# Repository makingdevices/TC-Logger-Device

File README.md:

<!-- Improved compatibility of back to top link: See: https://github.com/othneildrew/Best-README-Template/pull/73 -->

<!--
*** Thanks for checking out the Best-README-Template. If you have a suggestion
*** that would make this better, please fork the repo and create a pull request
*** or simply open an issue with the tag "enhancement".
*** Don't forget to give the project a star!
*** Thanks again! Now go create something AMAZING! :D
-->

<!-- PROJECT SHIELDS -->
<!--
*** I'm using markdown "reference style" links for readability.
*** Reference links are enclosed in brackets [ ] instead of parentheses ( ).
*** See the bottom of this document for the declaration of the reference variables
*** for contributors-url, forks-url, etc. This is an optional, concise syntax you may use.
*** https://www.markdownguide.org/basic-syntax/#reference-style-links
-->
[![Instagram][ig-shield]][ig-url]
[![PCBWAY][sponsor-shield]][sponsor-url]
[![Stargazers][stars-shield]][stars-url]
[![Issues][issues-shield]][issues-url]
[![LinkedIn][linkedin-shield]][linkedin-url]

<!-- PROJECT LOGO -->
<br />
<div align="center">

<h3 align="center">Making Devices</h3>

  <p align="center">
    Open Source projects where we struggle with engineering, electronics, coding and who knows what else... In this case, TC Logger Device is a very simple USB thermocouple reader, so hopefully you may find it interesting ;)
  </p>
</div>

<!-- TABLE OF CONTENTS -->
<details>
  <summary>Table of Contents</summary>
  <ol>
    <li>
      <a href="#about-the-project">About The Project</a>
      <ul>
        <li><a href="#built-with">Built With</a></li>
      </ul>
    </li>
    <li>
      <a href="#Build-one">Build one</a>
      <ul>
      </ul>
    </li>
    <li><a href="#usage">Usage</a></li>
    <li><a href="#roadmap">Roadmap</a></li>
    <li><a href="#license">License</a></li>
    <li><a href="#contact">Contact</a></li>
    <li><a href="#Sponsor">Sponsor</a></li>
  </ol>
</details>

<!-- ABOUT THE PROJECT -->
## About The Project

[![Bytes Counter Shot][product-screenshot]](https://makingdevices.com/TCLogger-Device)

TC Logger Device is a simple thermocouple USB reader: help you to measure any proccess you need using the USB protocol an a simple software developed in Python. The project was chosen to test the USB communication, explore the interface PC-Embedded system. The project is able to use two thermocouple at the same time and share the data to the computer at a speed of 5Hz. (5 samples per second). The main microprocessor is the PIC18F14K50.

<p align="right">(<a href="#readme-top">back to top</a>)</p>

### Built With

[![Microcontroller][PIC]][PIC-url]
[![MPLAB C][MPLAB-C]][MPLAB-C-url]
[![Kicad][kicad-shield]][kicad-url]
[![SPONSOR][sponsor-icon]][sponsor-url]

<p align="right">(<a href="#readme-top">back to top</a>)</p>

<!-- GETTING STARTED -->

## Build one
The project is finished and no further development will be made. The device is safe, stable and It was tested. 

1. Get the gerber files for the latest version: [V1.2b](https://github.com/makingdevices/TC-Logger-Device/blob/main/Gerber/v1.2b/ThermoDeviceLogger-v_1.2b.zip) 
2. Send them to a PCB manufacturer ([Our Sponsor is PCBWAY][sponsor-url])
3. You can read the user manual: [V1.0](https://github.com/makingdevices/TC-Logger-Device/blob/main/Output_PDF/Manual_ThermoLoggerv1_0.pdf) 

<p align="right">(<a href="#readme-top">back to top</a>)</p>

<!-- USAGE EXAMPLES -->
## Usage

Instructions of use:

- The LED will light up if a thermocouple is not detected.
- Use the Python software to communicate with the board.

You can read the user manual: [V1.0](https://github.com/makingdevices/TC-Logger-Device/blob/main/Output_PDF/Manual_ThermoLoggerv1_0.pdf) 

<p align="right">(<a href="#readme-top">back to top</a>)</p>

<!-- ROADMAP -->
## Roadmap

- [x] Finish the firmware for the PIC18F14K50
- [x] Validate firmware
- [x] Finish PC software
    - [x] Implement SCPI commands 
    - [x] Add data records 
    - [X] Improve thermocouple graphs
    - [x] Add Device Info page

See the [open issues](https://github.com/makingdevices/Thermo-device-logger/issues) for a full list of proposed features (and known issues).

State: Project <b>FINISHED</b> - 26/09/2023

Priority: <b>High</b>

<!-- SCPI -->
## SCPI Commands

- :MEAS  
  - :TC1
    - :INT?
    - :EXT?
    - :LED?
  - :TC2 
    - :INT?
    - :EXT?
    - :LED?
- :SET  
  - :TC1
    - :LED [AUTO|0|1] 
  - :TC2
    - :LED [AUTO|0|1] 
- :MODE   
  - :LED
    - :TC1?
    - :TC2?
- :CONF  
    - :APP?
    - :HW?
- *IDN?  
- :hello? 

<p align="right">(<a href="#readme-top">back to top</a>)</p>

<!-- LICENSE -->
## License

Distributed under three licenses:
- [Hardware](/License/HW_cern_ohl_s_v2.pdf)
- [Software](/License/SW_GPLv3.0.txt)
- [Documentation](/License/Documentation_CC-BY-SA-4.0.txt)

OSHW LICENSE: [ES000034](https://certification.oshwa.org/es000034.html)

[![GPL v3 License][license-shield]][license-url] 
<p align="right">(<a href="#readme-top">back to top</a>)</p>

<!-- CONTACT -->
## Contact

Making Devices - [@MakingDevices](https://www.instagram.com/makingdevices/)

Project Link: [https://github.com/makingdevices/TC-Logger-Device/](https://github.com/makingdevices/TC-Logger-Device/)

Other Links: [LinkTree](https://makingdevices.com/links/)

<p align="right">(<a href="#readme-top">back to top</a>)</p>

<!-- Sponsor -->
## Sponsor

[PCBWAY](https://www.pcbway.com/?from=makingdevices) is the most professional PCB manufacturer for prototyping and low-volume production to work with in the world. With more than a decade in the field, They are committed to meeting the needs of their customers from different industries in terms of quality, delivery, cost-effectiveness and any other demanding requests. As Sponsor of Making Devices, they will be in charge of all the PCBs for MDV, allowing both of us to grow together in a long term partnership. We hope you take them into account for your both personal and professional prototypes or products.

[![Sponsor Shot][sponsor-pcb-1]][sponsor-url]
[![Sponsor Shot][sponsor-pcb-2]][sponsor-url]

Should you want to colaborate with MakingDevices, you can buy a [TC Logger Device fully assembled and ready to use](https://www.pcbway.com/project/gifts_detail/TC_Logger_Device_5464ceb2.html)

<p align="right">(<a href="#readme-top">back to top</a>)</p>

<!-- MARKDOWN LINKS & IMAGES -->
<!-- https://www.markdownguide.org/basic-syntax/#reference-style-links -->
[contributors-shield]: https://img.shields.io/github/contributors/makingdevices/Thermo-device-logger.svg?style=for-the-badge
[contributors-url]: https://github.com/makingdevices/Thermo-device-logger/graphs/contributors
[forks-shield]: https://img.shields.io/github/forks/makingdevices/Thermo-device-logger.svg?style=for-the-badge
[forks-url]: https://github.com/makingdevices/Thermo-device-logger/network/members
[stars-shield]: https://img.shields.io/github/stars/makingdevices/Thermo-device-logger.svg?style=for-the-badge
[stars-url]: https://github.com/makingdevices/Thermo-device-logger/stargazers
[issues-shield]: https://img.shields.io/github/issues/makingdevices/Thermo-device-logger.svg?style=for-the-badge
[issues-url]: https://github.com/makingdevices/Thermo-device-logger/issues
[license-shield]: /images/license.png
[license-url]: https://github.com/makingdevices/Thermo-device-logger/tree/main/License
[linkedin-shield]: https://img.shields.io/badge/-LinkedIn-black.svg?style=for-the-badge&logo=linkedin&colorB=555
[linkedin-url]: https://www.linkedin.com/company/making-devices/
[sponsor-shield]: https://img.shields.io/badge/SPONSOR-PCBWAY-black.svg?style=for-the-badge&colorB=1200
[sponsor-url]: https://www.pcbway.com/?from=makingdevices
[sponsor-screenshot]: /images/PCB_sponsor.png
[sponsor-pcb-1]: /images/TClogger_pcb1.jpg
[sponsor-pcb-2]: /images/TClogger_pcb2.jpg
[product-screenshot]: images/screenshot.jpg
[PIC]: https://img.shields.io/badge/PIC18LF14K50-000000?style=for-the-badge
[PIC-url]: http://ww1.microchip.com/downloads/en/devicedoc/40001350f.pdf
[kicad-shield]: https://img.shields.io/badge/kicad-0b03fc?style=for-the-badge&logo=kicad&logoColor=white
[kicad-url]: https://www.kicad.org/
[YT-screenshot]: images/YT_assembly.PNG
[sponsor-icon]:  https://img.shields.io/badge/-PCBWAY-black.svg?style=for-the-badge&colorB=1200
[ig-shield]: https://img.shields.io/badge/instagram-a83297?style=for-the-badge&logo=instagram&logoColor=white
[ig-url]: https://www.instagram.com/makingdevices/
[MPLAB-C]: https://img.shields.io/badge/MPLAB%20C18-DD0031?style=for-the-badge&logo=C&logoColor=white
[MPLAB-C-url]: https://www.microchip.com/en-us/development-tool/SW006011
[Svelte.dev]: https://img.shields.io/badge/Svelte-4A4A55?style=for-the-badge&logo=svelte&logoColor=FF3E00
[Svelte-url]: https://svelte.dev/
[Laravel.com]: https://img.shields.io/badge/Laravel-FF2D20?style=for-the-badge&logo=laravel&logoColor=white
[Laravel-url]: https://laravel.com
[Bootstrap.com]: https://img.shields.io/badge/Bootstrap-563D7C?style=for-the-badge&logo=bootstrap&logoColor=white
[Bootstrap-url]: https://getbootstrap.com
[JQuery.com]: https://img.shields.io/badge/jQuery-0769AD?style=for-the-badge&logo=jquery&logoColor=white
[JQuery-url]: https://jquery.com

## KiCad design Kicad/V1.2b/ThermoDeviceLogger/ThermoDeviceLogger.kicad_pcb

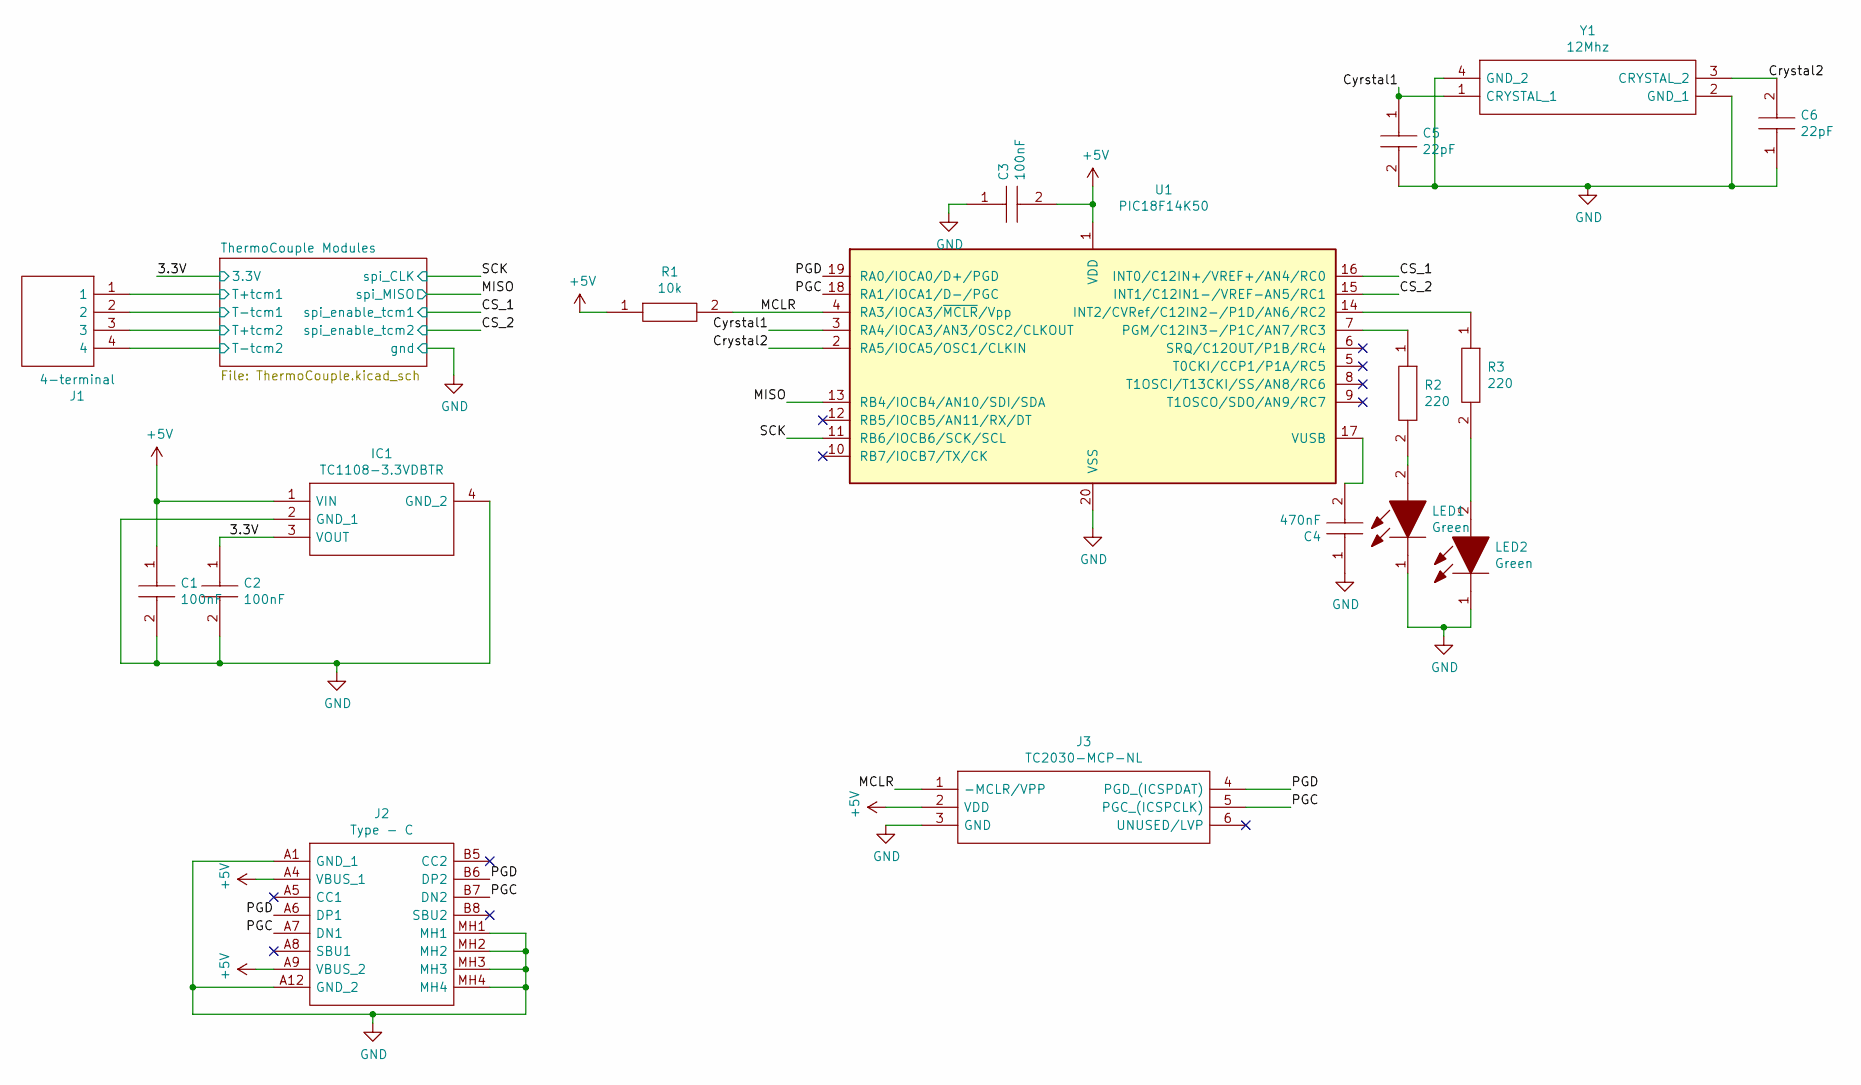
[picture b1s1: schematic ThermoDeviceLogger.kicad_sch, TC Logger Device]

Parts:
C1, C2, C3: 100nF; CAPC2012X140N; Manufacturer_Part_Number C0805C475M8RACTU
C4: 470nF; CAPC2012X140N; Manufacturer_Part_Number C0805C475M8RACTU
C5, C6: 22pF; CAPC2012X140N; Manufacturer_Part_Number C0805C475M8RACTU
IC1: TC1108-3.3VDBTR; SOT230P700X180-4N; Manufacturer_Part_Number TC1108-3.3VDBTR
J1: 4-terminal; 1751264; Manufacturer_Part_Number 1751264
J2: Type - C; 2169900003; Mouser Part Number 538-216990-0003
J3: TC2030-MCP-NL; Manufacturer_Part_Number TC2030-MCP-NL
LED1, LED2: Green; LEDC2012X90N; Manufacturer_Part_Number SML-H12V8TT86
R1: 10k; RESC2012X75N; Manufacturer_Part_Number ERJP6WF1303V
R2, R3: 220; RESC2012X75N; Manufacturer_Part_Number ERJP6WF1303V
U1: PIC18F14K50; SSOP-20_5.3x7.2mm_P0.65mm
Y1: 12Mhz; CX2520DB12000D0GPSC1; Manufacturer_Part_Number CX2520DB12000D0GPSC1

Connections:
+5V: C1.1, C3.2, IC1.1 (VIN), J2.A4 (VBUS_1), J2.A9 (VBUS_2), J3.2 (VDD), R1.1, U1.1 (VDD); also elsewhere on the board
/3.3V: C2.1, IC1.3 (VOUT); also elsewhere on the board
/CS_1: U1.16 (INT0/C12IN+/VREF+/AN4/RC0); also elsewhere on the board
/CS_2: U1.15 (INT1/C12IN1-/VREF-AN5/RC1); also elsewhere on the board
/Crystal2: C6.2, U1.2 (RA5/IOCA5/OSC1/CLKIN), Y1.3 (CRYSTAL_2)
/Cyrstal1: C5.1, U1.3 (RA4/IOCA3/AN3/OSC2/CLKOUT), Y1.1 (CRYSTAL_1)
/MCLR: J3.1 (-MCLR/VPP), R1.2, U1.4 (RA3/IOCA3/~MCLR/Vpp); also elsewhere on the board
/MISO: U1.13 (RB4/IOCB4/AN10/SDI/SDA); also elsewhere on the board
/PGC: J2.A7 (DN1), J2.B7 (DN2), J3.5 (PGC_(ICSPCLK)), U1.18 (RA1/IOCA1/D-/PGC); also elsewhere on the board
/PGD: J2.A6 (DP1), J2.B6 (DP2), J3.4 (PGD_(ICSPDAT)), U1.19 (RA0/IOCA0/D+/PGD); also elsewhere on the board
/SCK: U1.11 (RB6/IOCB6/SCK/SCL); also elsewhere on the board
/ThermoCouple Modules/T+tcm1: J1.1; also elsewhere on the board
/ThermoCouple Modules/T+tcm2: J1.3; also elsewhere on the board
/ThermoCouple Modules/T-tcm1: J1.2; also elsewhere on the board
/ThermoCouple Modules/T-tcm2: J1.4; also elsewhere on the board
GND: C1.2, C2.2, C3.1, C4.1, C5.2, C6.1, IC1.2 (GND_1), IC1.4 (GND_2), J2.A1 (GND_1), J2.A12 (GND_2), J2.MH1, J2.MH2, J2.MH3, J2.MH4, J3.3 (GND), LED1.1, LED2.1, U1.20 (VSS), Y1.2 (GND_1), Y1.4 (GND_2); also elsewhere on the board
unnamed: C4.2, U1.17 (VUSB)
unnamed: LED1.2, R2.2
unnamed: LED2.2, R3.2
unnamed: R2.1, U1.7 (PGM/C12IN3-/P1C/AN7/RC3)
unnamed: R3.1, U1.14 (INT2/CVRef/C12IN2-/P1D/AN6/RC2)

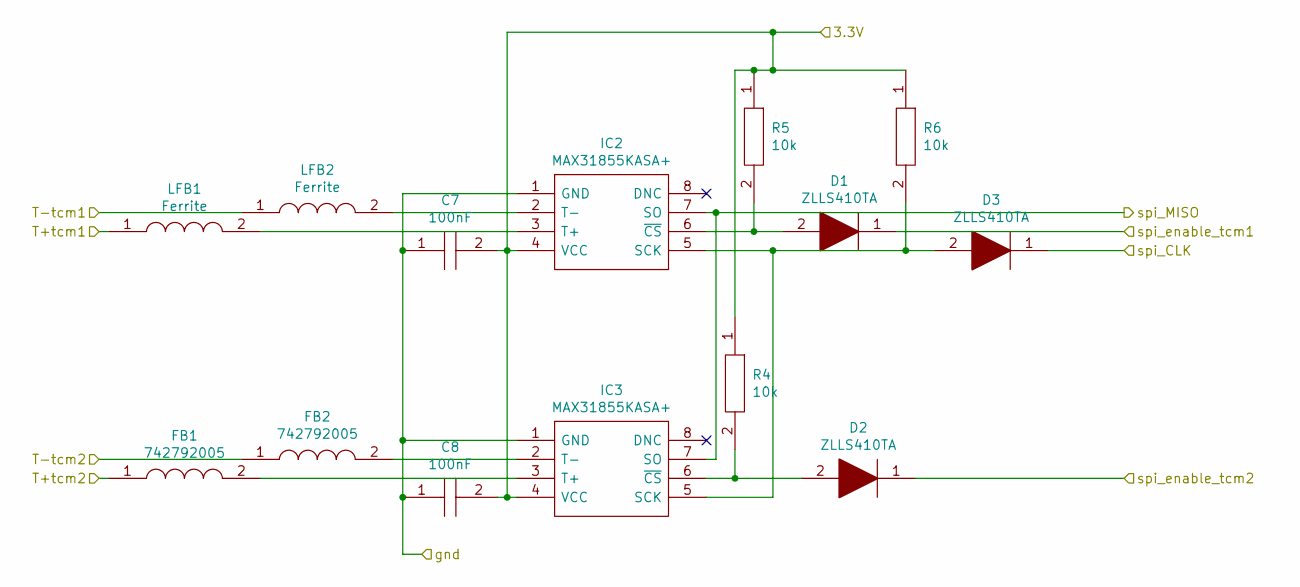
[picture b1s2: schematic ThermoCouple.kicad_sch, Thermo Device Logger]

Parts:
C7, C8: 100nF; CAPC2012X140N; Manufacturer_Part_Number C0805C475M8RACTU
D1, D2, D3: ZLLS410TA; SOD2513X120N; Manufacturer_Part_Number ZLLS410TA
FB1, FB2: 742792005; CAPC2012X90N; Manufacturer_Part_Number 742792005
IC2, IC3: MAX31855KASA+; SOIC127P600X175-8N; Manufacturer_Part_Number MAX31855KASA+
LFB1, LFB2: Ferrite; CAPC2012X90N; Manufacturer_Part_Number 742792005
R4, R5, R6: 10k; RESC2012X75N; Manufacturer_Part_Number ERJP6WF1303V

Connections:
/3.3V: C7.2, C8.2, IC2.4 (VCC), IC3.4 (VCC), R4.1, R5.1, R6.1; also elsewhere on the board
/CS_1: D1.1; also elsewhere on the board
/CS_2: D2.1; also elsewhere on the board
/MISO: IC2.7 (SO), IC3.7 (SO); also elsewhere on the board
/SCK: D3.1; also elsewhere on the board
/ThermoCouple Modules/T+tcm1: LFB1.1; also elsewhere on the board
/ThermoCouple Modules/T+tcm2: FB1.1; also elsewhere on the board
/ThermoCouple Modules/T-tcm1: LFB2.1; also elsewhere on the board
/ThermoCouple Modules/T-tcm2: FB2.1; also elsewhere on the board
GND: C7.1, C8.1, IC2.1 (GND), IC3.1 (GND); also elsewhere on the board
unnamed: D1.2, IC2.6 (~CS), R5.2
unnamed: D2.2, IC3.6 (~CS), R4.2
unnamed: D3.2, IC2.5 (SCK), IC3.5 (SCK), R6.2
unnamed: FB1.2, IC3.3 (T+)
unnamed: FB2.2, IC3.2 (T-)
unnamed: IC2.2 (T-), LFB2.2
unnamed: IC2.3 (T+), LFB1.2

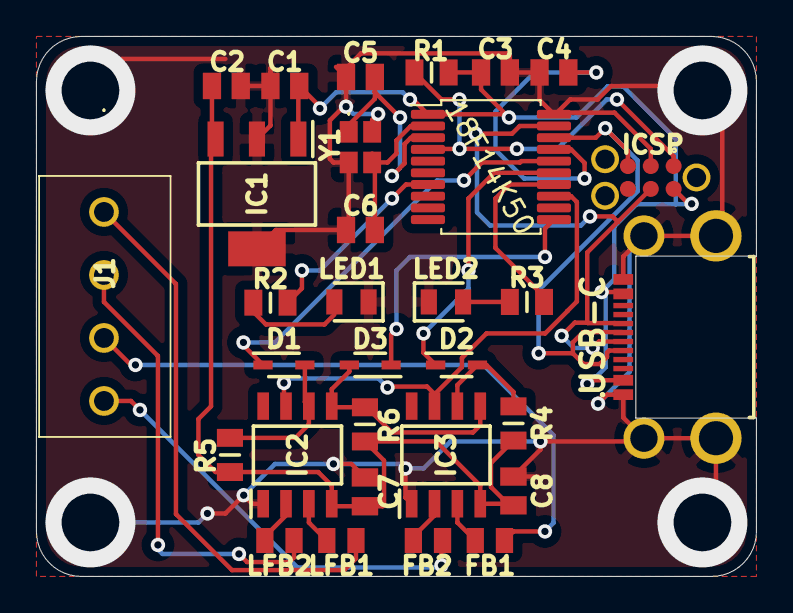
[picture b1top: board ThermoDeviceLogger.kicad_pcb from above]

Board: 2 copper layers, 40.0 x 30.0 mm, 31 parts (0 on the bottom side), 28 nets.

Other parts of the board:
ICSP: TC2030-MCP-NL
USB-C: Type - C; 2169900003

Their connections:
+5V: ICSP.2, USB-C.A4, USB-C.A9; also elsewhere on the board
/MCLR: ICSP.1; also elsewhere on the board
/PGC: ICSP.5, USB-C.A7, USB-C.B7; also elsewhere on the board
/PGD: ICSP.4, USB-C.A6, USB-C.B6; also elsewhere on the board
GND: ICSP.3, USB-C.A1, USB-C.A12, USB-C.MH1, USB-C.MH2, USB-C.MH3, USB-C.MH4; also elsewhere on the board

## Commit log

2022-12-19 Adding new project
    Update!
2023-01-04 Reconnect tool. // Not connected thermocouple detection
2023-01-04 Adding new features
2023-01-04 Added dynamic graphs for the thermocouples
2023-01-06 Updating README
2023-01-06 updates to the readme
2023-01-06 no message
2023-02-08 SCPI Commands...
2023-02-22 Almost finished
2023-02-22 Updated TO-DO list
2023-02-23 Stable Firmware
2023-03-06 Testing firmware
2023-03-20 Firmware 1.02 done. Validation pending...
2023-03-23 1.2b Production version finished.
2023-04-15 Kicad files
2023-04-19 Updated software for PC
2023-04-20 Finishing touches
2023-04-24 Reconnect function for PC software
2023-09-18 Organize PC software files
2023-09-18 Latest v1.1 software version and user manual
2023-09-18 new pic
2023-09-24 New 1.50 FW release. Final version for both SW and HW. I also uploaded some python scripts and compiled versions so it is easier to communicate with the board and any PC.
2023-11-22 Commit manual
2025-01-28 Uploading .exe file
